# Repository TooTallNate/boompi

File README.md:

# Boompi

Boompi turns a Raspberry Pi into a boombox: a complete, flashable
appliance OS for building your own - Bluetooth/AirPlay/Spotify audio,
a touchscreen now-playing UI, game emulation, battery awareness, and
remote control over Wi-Fi or BLE (web + iOS). It grew out of two
custom builds and is becoming something anyone can put in a box:

- **`boompid`** - Rust backend daemon: Bluetooth (BlueZ), Spotify Connect
  (librespot), AirPlay (shairport-sync), PipeWire volume, INA260 battery
  telemetry, FFT visualizer, album art. Serves a WebSocket/HTTP API.
- **`boompi-ui`** - Slint touchscreen UI: renders directly on DRM/KMS on the
  boombox, or as a desktop app on a laptop for development.
- **`web/`** - settings web app served by the box; **`web-remote/`** - the
  hosted Web Bluetooth remote ([boompi.n8.io](https://boompi.n8.io));
  **`ios/`** - the native iOS app.
- **`buildroot/`** - flashable, pre-configured SD card images (silent boot,
  A/B self-updates, first-boot setup). Box-specific hardware (display
  panel, DAC, battery sensor, wiring) is described by an on-device
  profile, not baked into the image - one image boots every build.

The v1 stack (Node.js + Next.js + Chromium kiosk) lives on the `v1` branch.
The (shipped) design and phased plan is in [`docs/PLAN.md`](docs/PLAN.md),
the A/B update system in [`docs/UPDATES.md`](docs/UPDATES.md), and
future work in [`docs/ROADMAP.md`](docs/ROADMAP.md).

Releases are cut with [changesets](.changeset/README.md): merging the
"Version Packages" PR publishes a GitHub Release with flashable images
and OTA assets; every green build of `main` also refreshes the rolling
`edge` prerelease. The boxes update themselves from either channel
(Settings → Software).

## Development

No hardware needed for UI work:

```sh
make sim   # terminal 1: backend with simulated sources/battery/visualizer
make ui    # terminal 2: the UI, connected to the local sim
```

Against a real boombox:

```sh
make ui BACKEND=ws://boombox.local:3001/ws
```

Other targets: `make check`, `make test`, `make fmt`, `make clippy`.

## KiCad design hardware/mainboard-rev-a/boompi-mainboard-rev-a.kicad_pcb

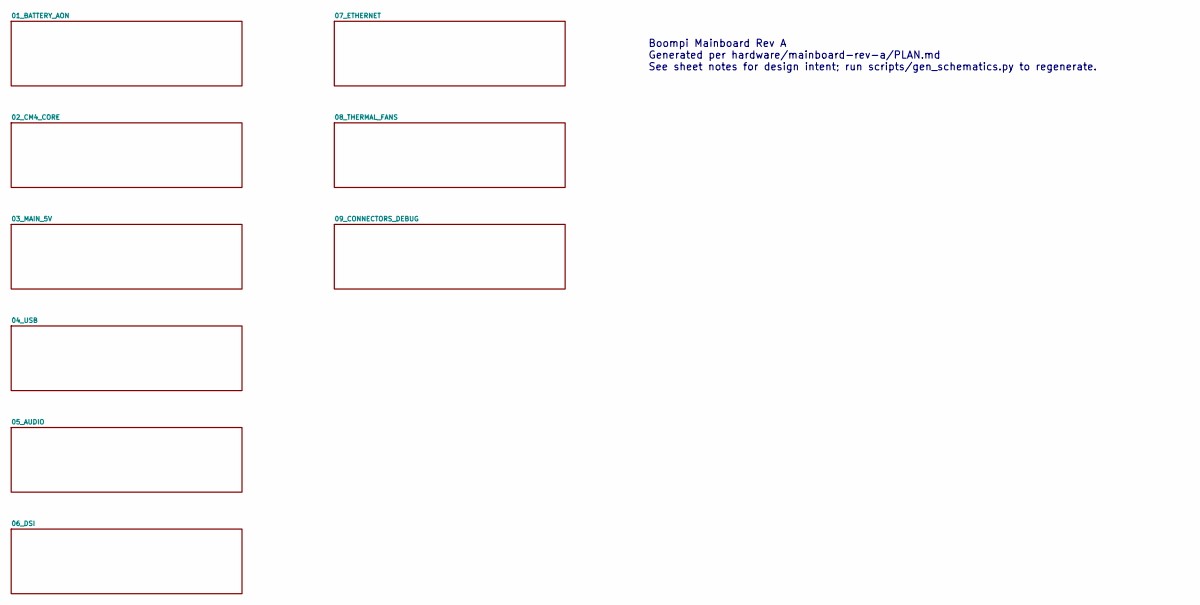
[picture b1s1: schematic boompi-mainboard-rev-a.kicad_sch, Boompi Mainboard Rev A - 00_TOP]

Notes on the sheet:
Boompi Mainboard Rev A Generated per hardware/mainboard-rev-a/PLAN.md See sheet notes for design intent; run scripts/gen_schematics.py to regenerate.

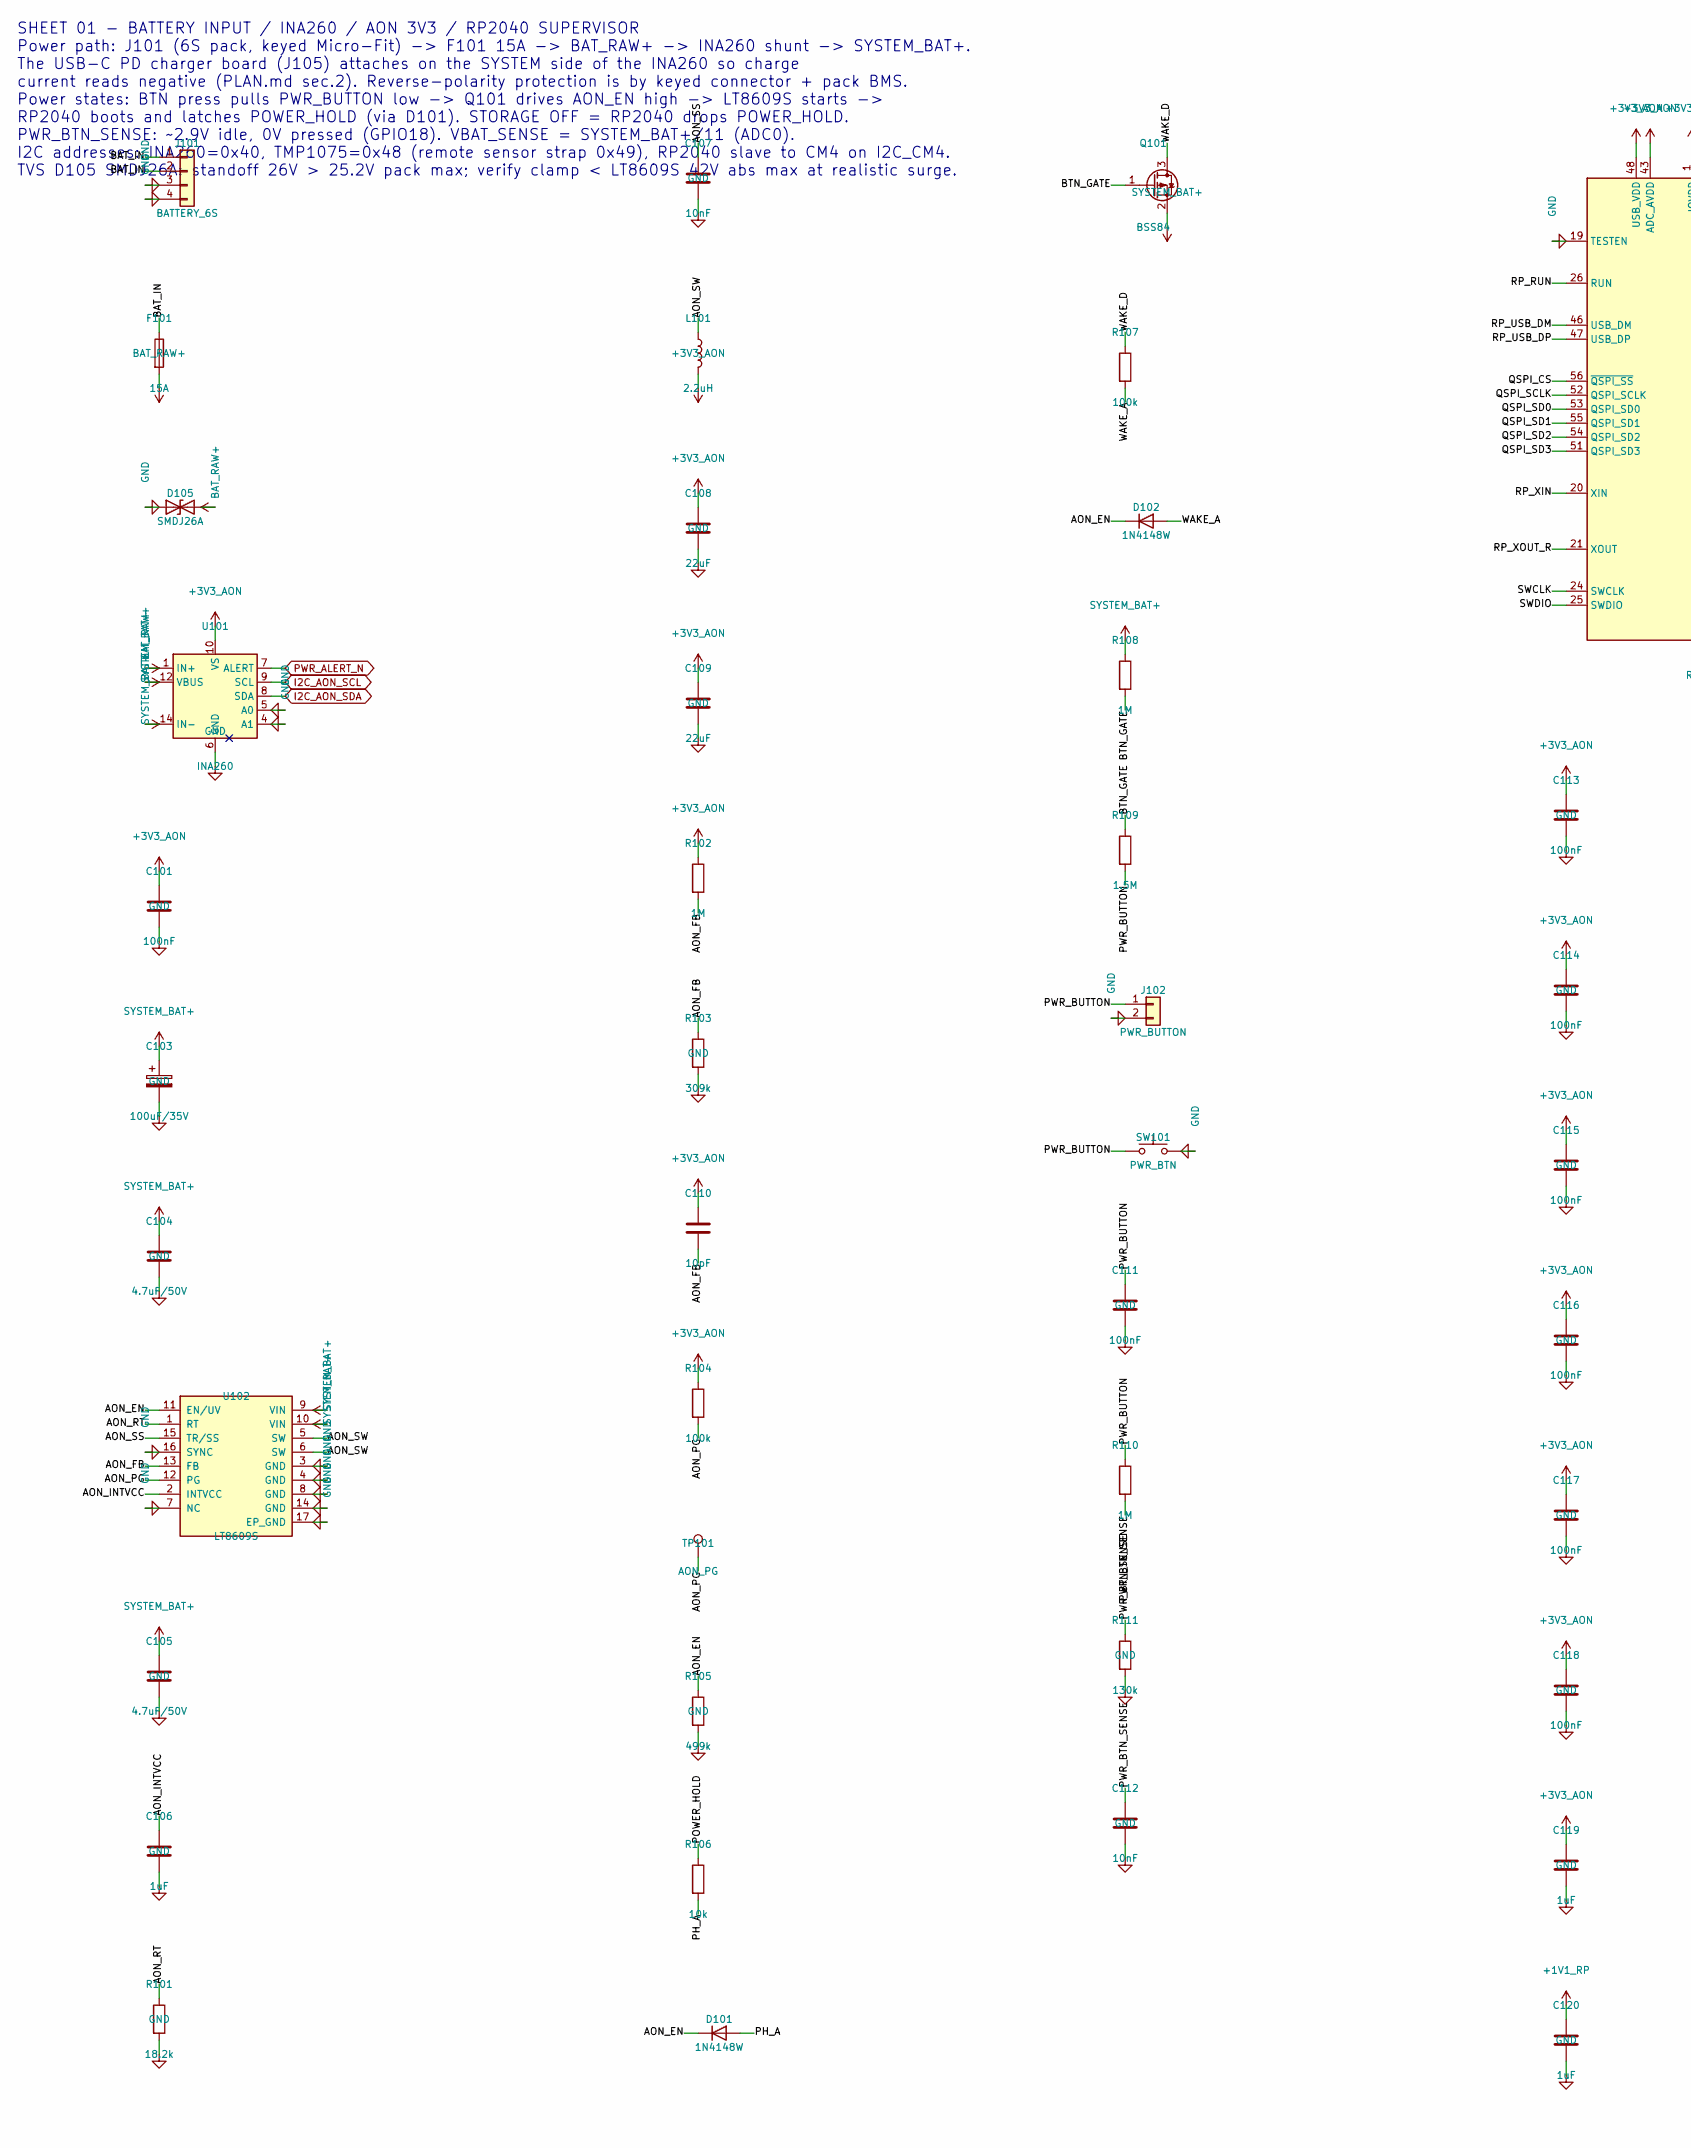
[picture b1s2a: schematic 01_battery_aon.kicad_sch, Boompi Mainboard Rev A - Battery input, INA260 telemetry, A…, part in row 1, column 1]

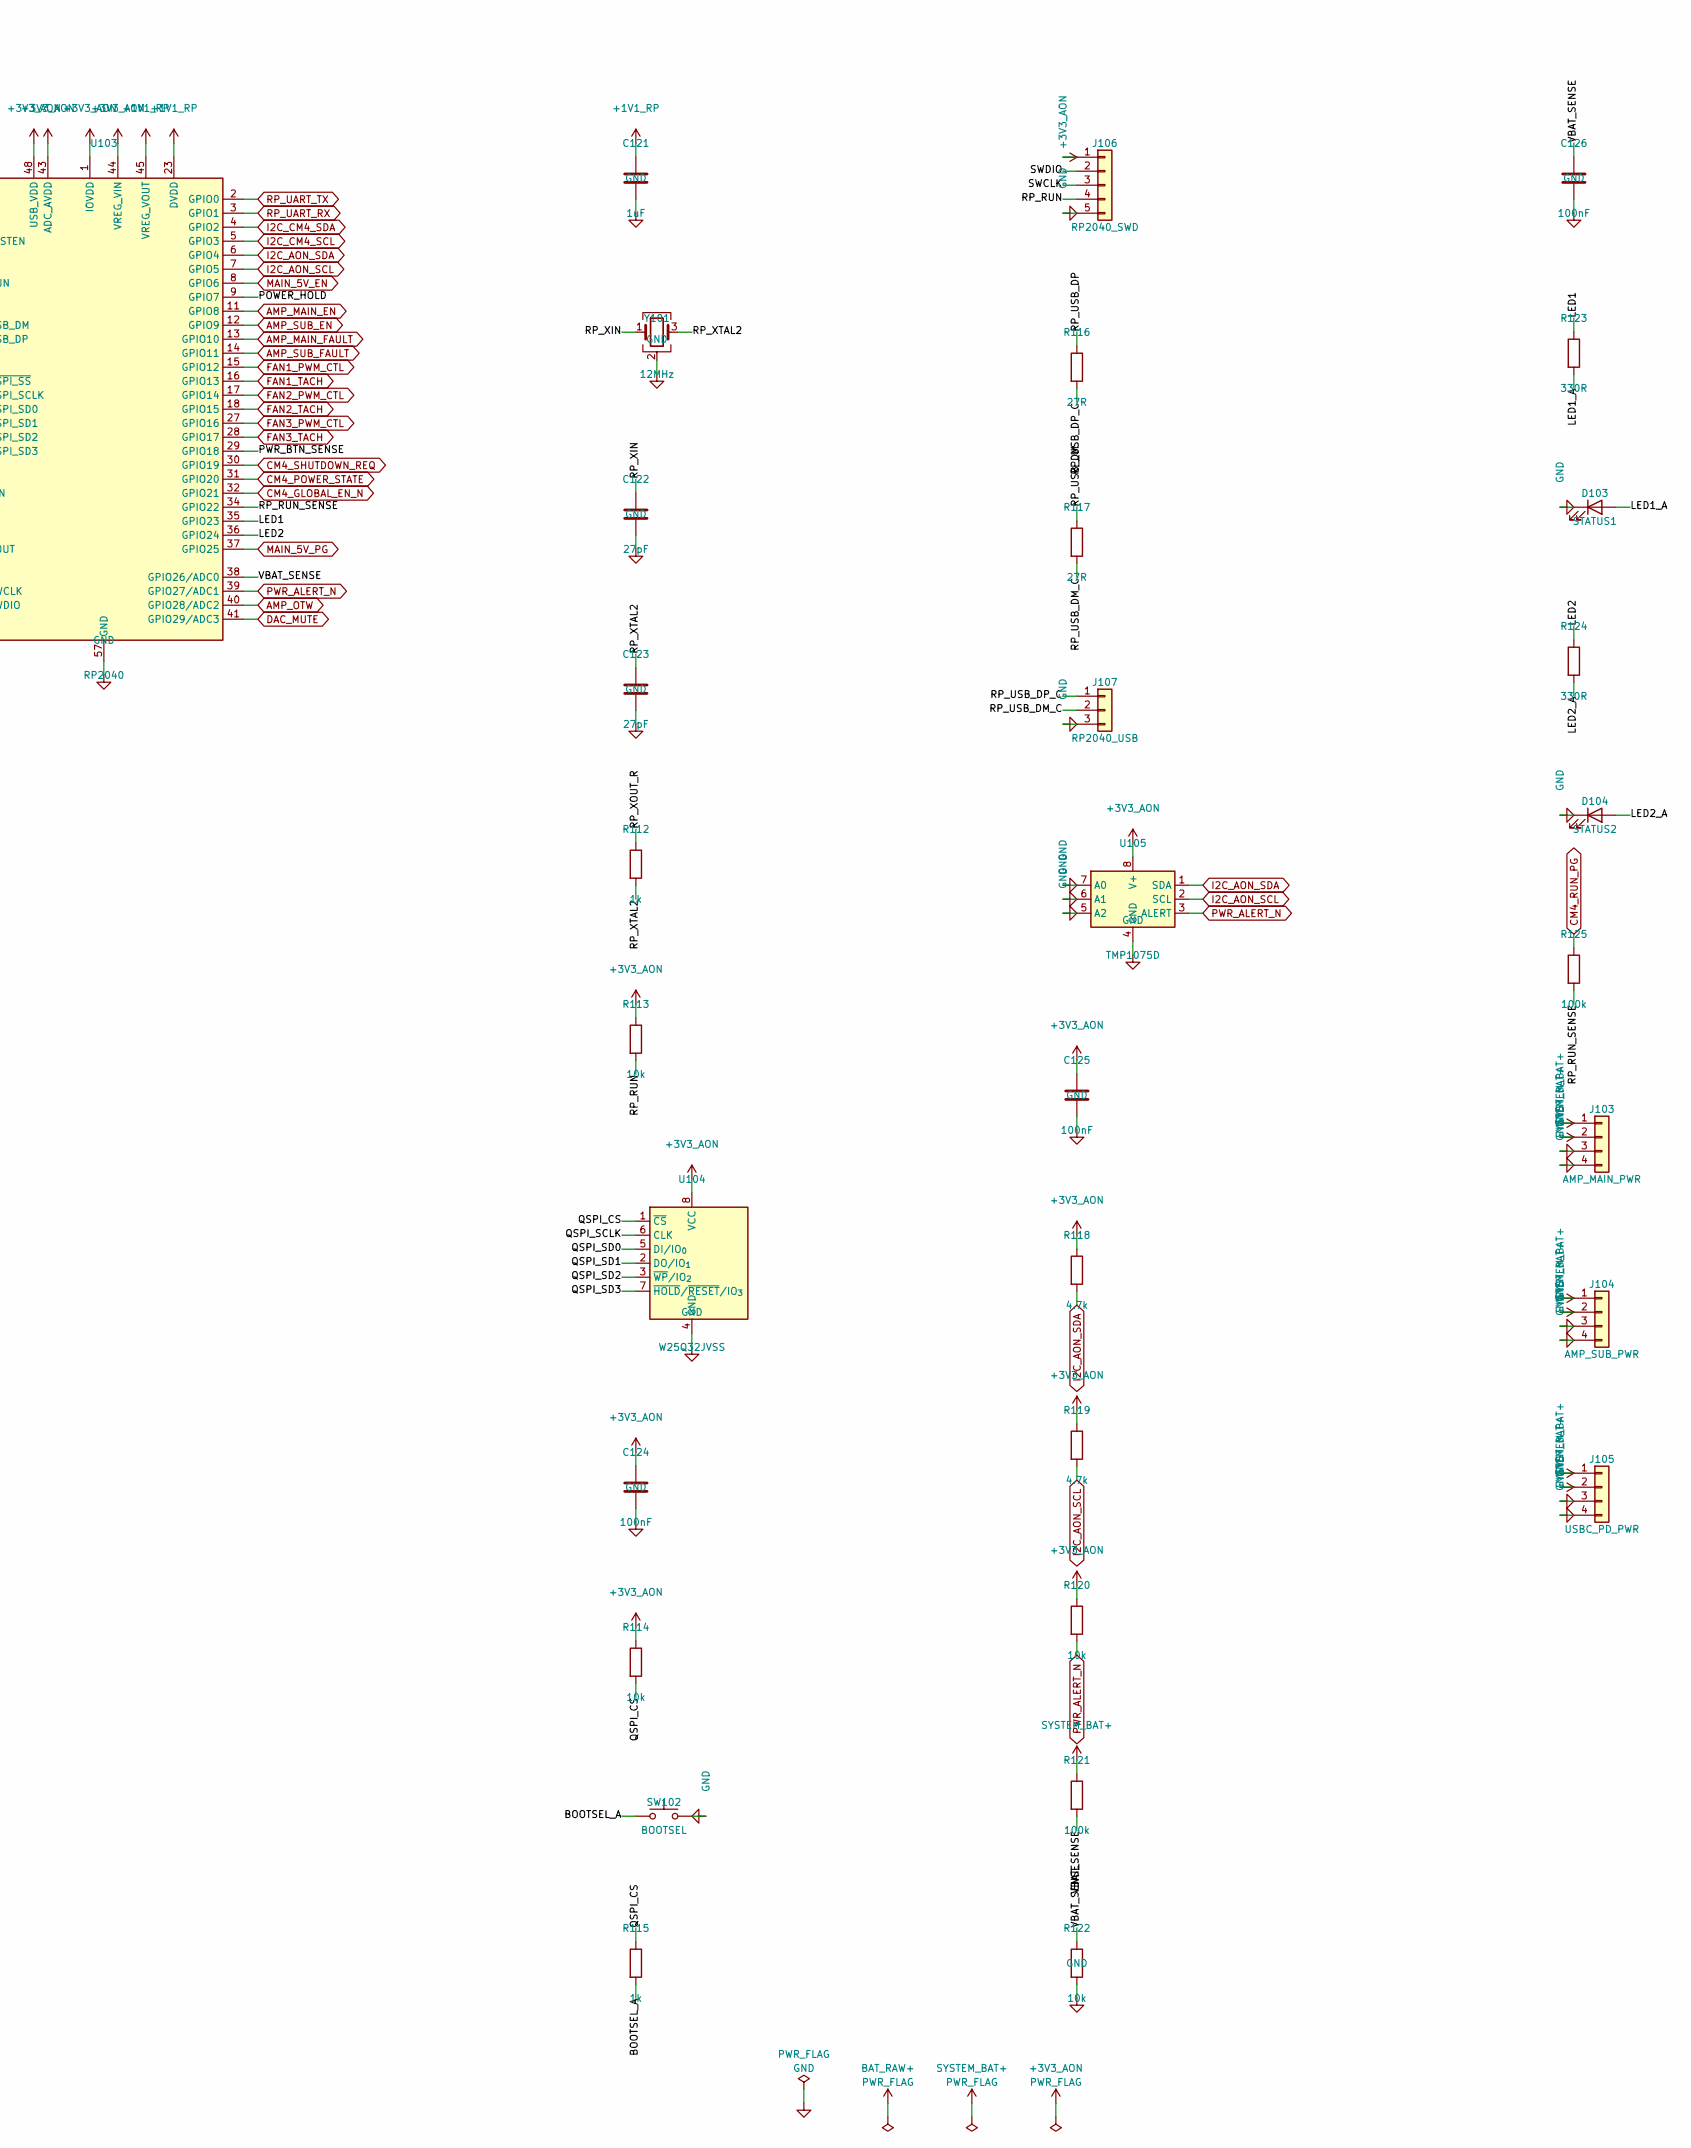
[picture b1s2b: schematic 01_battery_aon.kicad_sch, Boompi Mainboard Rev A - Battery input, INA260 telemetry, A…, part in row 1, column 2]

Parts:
C101, C111, C113, C114, C115, C116, C117, C118, C124, C125, C126: 100nF; C_0603_1608Metric
C103: 100uF/35V; CP_Elec_8x10.5; MPN Panasonic EEE-FK1V101P
C104, C105: 4.7uF/50V; C_1210_3225Metric
C106, C119, C120, C121: 1uF; C_0603_1608Metric
C107, C112: 10nF; C_0603_1608Metric
C108, C109: 22uF; C_1210_3225Metric
C110: 10pF; C_0603_1608Metric
C122, C123: 27pF; C_0603_1608Metric
D101, D102: 1N4148W; D_SOD-123; MPN 1N4148W-7-F
D103: STATUS1; LED_0603_1608Metric
D104: STATUS2; LED_0603_1608Metric
D105: SMDJ26A; D_SMC; MPN Littelfuse SMDJ26A
F101: 15A; Fuse_Littelfuse-NANO2-451_453; MPN Littelfuse 0451015.MRL
J101: BATTERY_6S; Molex_Micro-Fit_3.0_43650-0415_1x04_P3.00mm_Vertical; MPN Molex 43650-0415
J102: PWR_BUTTON; JST_PH_B2B-PH-K_1x02_P2.00mm_Vertical; MPN JST B2B-PH-K-S
J103: AMP_MAIN_PWR; Molex_Micro-Fit_3.0_43650-0415_1x04_P3.00mm_Vertical; MPN Molex 43650-0415
J104: AMP_SUB_PWR; Molex_Micro-Fit_3.0_43650-0415_1x04_P3.00mm_Vertical; MPN Molex 43650-0415
J105: USBC_PD_PWR; Molex_Micro-Fit_3.0_43650-0415_1x04_P3.00mm_Vertical; MPN Molex 43650-0415
J106: RP2040_SWD; PinHeader_1x05_P2.54mm_Vertical
J107: RP2040_USB; PinHeader_1x03_P2.54mm_Vertical
L101: 2.2uH; L_Coilcraft_XxL4020; MPN Coilcraft XFL4020-222ME
Q101: BSS84; SOT-23; MPN onsemi BSS84LT1G
R101: 18.2k; R_0603_1608Metric
R102, R108, R110: 1M; R_0603_1608Metric
R103: 309k; R_0603_1608Metric
R104, R107, R121, R125: 100k; R_0603_1608Metric
R105: 499k; R_0603_1608Metric
R106, R113, R114, R120, R122: 10k; R_0603_1608Metric
R109: 1.5M; R_0603_1608Metric
R111: 130k; R_0603_1608Metric
R112, R115: 1k; R_0603_1608Metric
R116, R117: 27R; R_0603_1608Metric
R118, R119: 4.7k; R_0603_1608Metric
R123, R124: 330R; R_0603_1608Metric
SW101: PWR_BTN; SW_SPST_TL3342; MPN E-Switch TL3342F160QG
SW102: BOOTSEL; SW_SPST_TL3342
TP101: AON_PG; TestPoint_Pad_D1.5mm
U101: INA260; TSSOP-16_4.4x5mm_P0.65mm; MPN TI INA260AIPW
U102: LT8609S; LT8609S_LQFN16_3x3mm; MPN ADI LT8609SEV#PBF
U103: RP2040; QFN-56-1EP_7x7mm_P0.4mm_EP3.2x3.2mm; MPN Raspberry Pi RP2040
U104: W25Q32JVSS; SOIC-8_5.3x5.3mm_P1.27mm; MPN Winbond W25Q32JVSSIQ
U105: TMP1075D; SOIC-8_3.9x4.9mm_P1.27mm; MPN TI TMP1075DR
Y101: 12MHz; Crystal_SMD_3225-4Pin_3.2x2.5mm; MPN Abracon ABM8-12.000MHZ-B2-T

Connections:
+1V1_RP: C120.1, C121.1, U103.23 (DVDD), U103.45 (VREG_VOUT), U103.50 (DVDD)
+3V3_AON: C101.1, C108.1, C109.1, C110.1, C113.1, C114.1, C115.1, C116.1, C117.1, C118.1, C119.1, C124.1, C125.1, J106.1, L101.2, R102.1, R104.1, R113.1, R114.1, R118.1, R119.1, R120.1, U101.10 (VS), U103.1 (IOVDD), U103.10 (IOVDD), U103.22 (IOVDD), U103.33 (IOVDD), U103.42 (IOVDD), U103.43 (ADC_AVDD), U103.44 (VREG_VIN), U103.48 (USB_VDD), U103.49 (IOVDD), U104.8 (VCC), U105.8 (V+); also elsewhere on the board
/01_BATTERY_AON/AON_EN: D101.1 (K), D102.1 (K), R105.1, U102.11 (EN/UV)
/01_BATTERY_AON/AON_FB: C110.2, R102.2, R103.1, U102.13 (FB)
/01_BATTERY_AON/AON_INTVCC: C106.1, U102.2 (INTVCC)
/01_BATTERY_AON/AON_PG: R104.2, TP101.1, U102.12 (PG)
/01_BATTERY_AON/AON_RT: R101.1, U102.1 (RT)
/01_BATTERY_AON/AON_SS: C107.1, U102.15 (TR/SS)
/01_BATTERY_AON/AON_SW: L101.1, U102.5 (SW), U102.6 (SW)
/01_BATTERY_AON/BAT_IN: F101.1, J101.1, J101.2
/01_BATTERY_AON/BOOTSEL_A: R115.2, SW102.1
/01_BATTERY_AON/BTN_GATE: Q101.1 (G), R108.2, R109.1
/01_BATTERY_AON/LED1: R123.1, U103.35 (GPIO23)
/01_BATTERY_AON/LED1_A: D103.2 (A), R123.2
/01_BATTERY_AON/LED2: R124.1, U103.36 (GPIO24)
/01_BATTERY_AON/LED2_A: D104.2 (A), R124.2
/01_BATTERY_AON/PH_A: D101.2 (A), R106.2
/01_BATTERY_AON/POWER_HOLD: R106.1, U103.9 (GPIO7)
/01_BATTERY_AON/PWR_BTN_SENSE: C112.1, R110.2, R111.1, U103.29 (GPIO18)
/01_BATTERY_AON/PWR_BUTTON: C111.1, J102.1, R109.2, R110.1, SW101.1
/01_BATTERY_AON/QSPI_CS: R114.2, R115.1, U103.56 (~QSPI_SS), U104.1 (~CS)
/01_BATTERY_AON/QSPI_SCLK: U103.52 (QSPI_SCLK), U104.6 (CLK)
/01_BATTERY_AON/QSPI_SD0: U103.53 (QSPI_SD0), U104.5 (DI/IO_{0})
/01_BATTERY_AON/QSPI_SD1: U103.55 (QSPI_SD1), U104.2 (DO/IO_{1})
/01_BATTERY_AON/QSPI_SD2: U103.54 (QSPI_SD2), U104.3 (~WP/IO_{2})
/01_BATTERY_AON/QSPI_SD3: U103.51 (QSPI_SD3), U104.7 (~HOLD/~RESET/IO_{3})
/01_BATTERY_AON/RP_RUN: J106.4, R113.2, U103.26 (RUN)
/01_BATTERY_AON/RP_RUN_SENSE: R125.2, U103.34 (GPIO22)
/01_BATTERY_AON/RP_USB_DM: R117.1, U103.46 (USB_DM)
/01_BATTERY_AON/RP_USB_DM_C: J107.2, R117.2
/01_BATTERY_AON/RP_USB_DP: R116.1, U103.47 (USB_DP)
/01_BATTERY_AON/RP_USB_DP_C: J107.1, R116.2
/01_BATTERY_AON/RP_XIN: C122.1, U103.20 (XIN), Y101.1
/01_BATTERY_AON/RP_XOUT_R: R112.1, U103.21 (XOUT)
/01_BATTERY_AON/RP_XTAL2: C123.1, R112.2, Y101.3
/01_BATTERY_AON/SWCLK: J106.3, U103.24 (SWCLK)
/01_BATTERY_AON/SWDIO: J106.2, U103.25 (SWDIO)
/01_BATTERY_AON/VBAT_SENSE: C126.1, R121.2, R122.1, U103.38 (GPIO26/ADC0)
/01_BATTERY_AON/WAKE_A: D102.2 (A), R107.2
/01_BATTERY_AON/WAKE_D: Q101.3 (D), R107.1
AMP_MAIN_EN: U103.11 (GPIO8); also elsewhere on the board
AMP_MAIN_FAULT: U103.13 (GPIO10); also elsewhere on the board
AMP_OTW: U103.40 (GPIO28/ADC2); also elsewhere on the board
AMP_SUB_EN: U103.12 (GPIO9); also elsewhere on the board
AMP_SUB_FAULT: U103.14 (GPIO11); also elsewhere on the board
BAT_RAW+: D105.2 (A2), F101.2, U101.1 (IN+), U101.2 (IN+), U101.3 (IN+)
CM4_GLOBAL_EN_N: U103.32 (GPIO21); also elsewhere on the board
CM4_POWER_STATE: U103.31 (GPIO20); also elsewhere on the board
CM4_RUN_PG: R125.1; also elsewhere on the board
CM4_SHUTDOWN_REQ: U103.30 (GPIO19); also elsewhere on the board
DAC_MUTE: U103.41 (GPIO29/ADC3); also elsewhere on the board
FAN1_PWM_CTL: U103.15 (GPIO12); also elsewhere on the board
FAN1_TACH: U103.16 (GPIO13); also elsewhere on the board
FAN2_PWM_CTL: U103.17 (GPIO14); also elsewhere on the board
FAN2_TACH: U103.18 (GPIO15); also elsewhere on the board
FAN3_PWM_CTL: U103.27 (GPIO16); also elsewhere on the board
FAN3_TACH: U103.28 (GPIO17); also elsewhere on the board
GND: C101.2, C103.2, C104.2, C105.2, C106.2, C107.2, C108.2, C109.2, C111.2, C112.2, C113.2, C114.2, C115.2, C116.2, C117.2, C118.2, C119.2, C120.2, C121.2, C122.2, C123.2, C124.2, C125.2, C126.2, D103.1 (K), D104.1 (K), D105.1 (A1), J101.3, J101.4, J102.2, J103.3, J103.4, J104.3, J104.4, J105.3, J105.4, J106.5, J107.3, R101.2, R103.2, R105.2, R111.2, R122.2, SW101.2, SW102.2, U101.4 (A1), U101.5 (A0), U101.6 (GND), U101.11 (GND), U102.3 (GND), U102.4 (GND), U102.7 (NC), U102.8 (GND), U102.14 (GND), U102.16 (SYNC), U102.17 (EP_GND), U103.19 (TESTEN), U103.57 (GND), U104.4 (GND), U105.4 (GND), U105.5 (A2), U105.6 (A1), U105.7 (A0), Y101.2 (G), Y101.4 (G); also elsewhere on the board
I2C_AON_SCL: R119.2, U101.9 (SCL), U103.7 (GPIO5), U105.2 (SCL); also elsewhere on the board
I2C_AON_SDA: R118.2, U101.8 (SDA), U103.6 (GPIO4), U105.1 (SDA); also elsewhere on the board
I2C_CM4_SCL: U103.5 (GPIO3); also elsewhere on the board
I2C_CM4_SDA: U103.4 (GPIO2); also elsewhere on the board
MAIN_5V_EN: U103.8 (GPIO6); also elsewhere on the board
MAIN_5V_PG: U103.37 (GPIO25); also elsewhere on the board
PWR_ALERT_N: R120.2, U101.7 (ALERT), U103.39 (GPIO27/ADC1), U105.3 (ALERT)
RP_UART_RX: U103.3 (GPIO1); also elsewhere on the board
RP_UART_TX: U103.2 (GPIO0); also elsewhere on the board
SYSTEM_BAT+: C103.1, C104.1, C105.1, J103.1, J103.2, J104.1, J104.2, J105.1, J105.2, Q101.2 (S), R108.1, R121.1, U101.12 (VBUS), U101.14 (IN-), U101.15 (IN-), U101.16 (IN-), U102.9 (VIN), U102.10 (VIN); also elsewhere on the board

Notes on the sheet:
SHEET 01 - BATTERY INPUT / INA260 / AON 3V3 / RP2040 SUPERVISOR Power path: J101 (6S pack, keyed Micro-Fit) -> F101 15A -> BAT_RAW+ -> INA260 shunt -> SYSTEM_BAT+. The USB-C PD charger board (J105) attaches on the SYSTEM side of the INA260 so charge current reads negative (PLAN.md sec.2). Reverse-p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

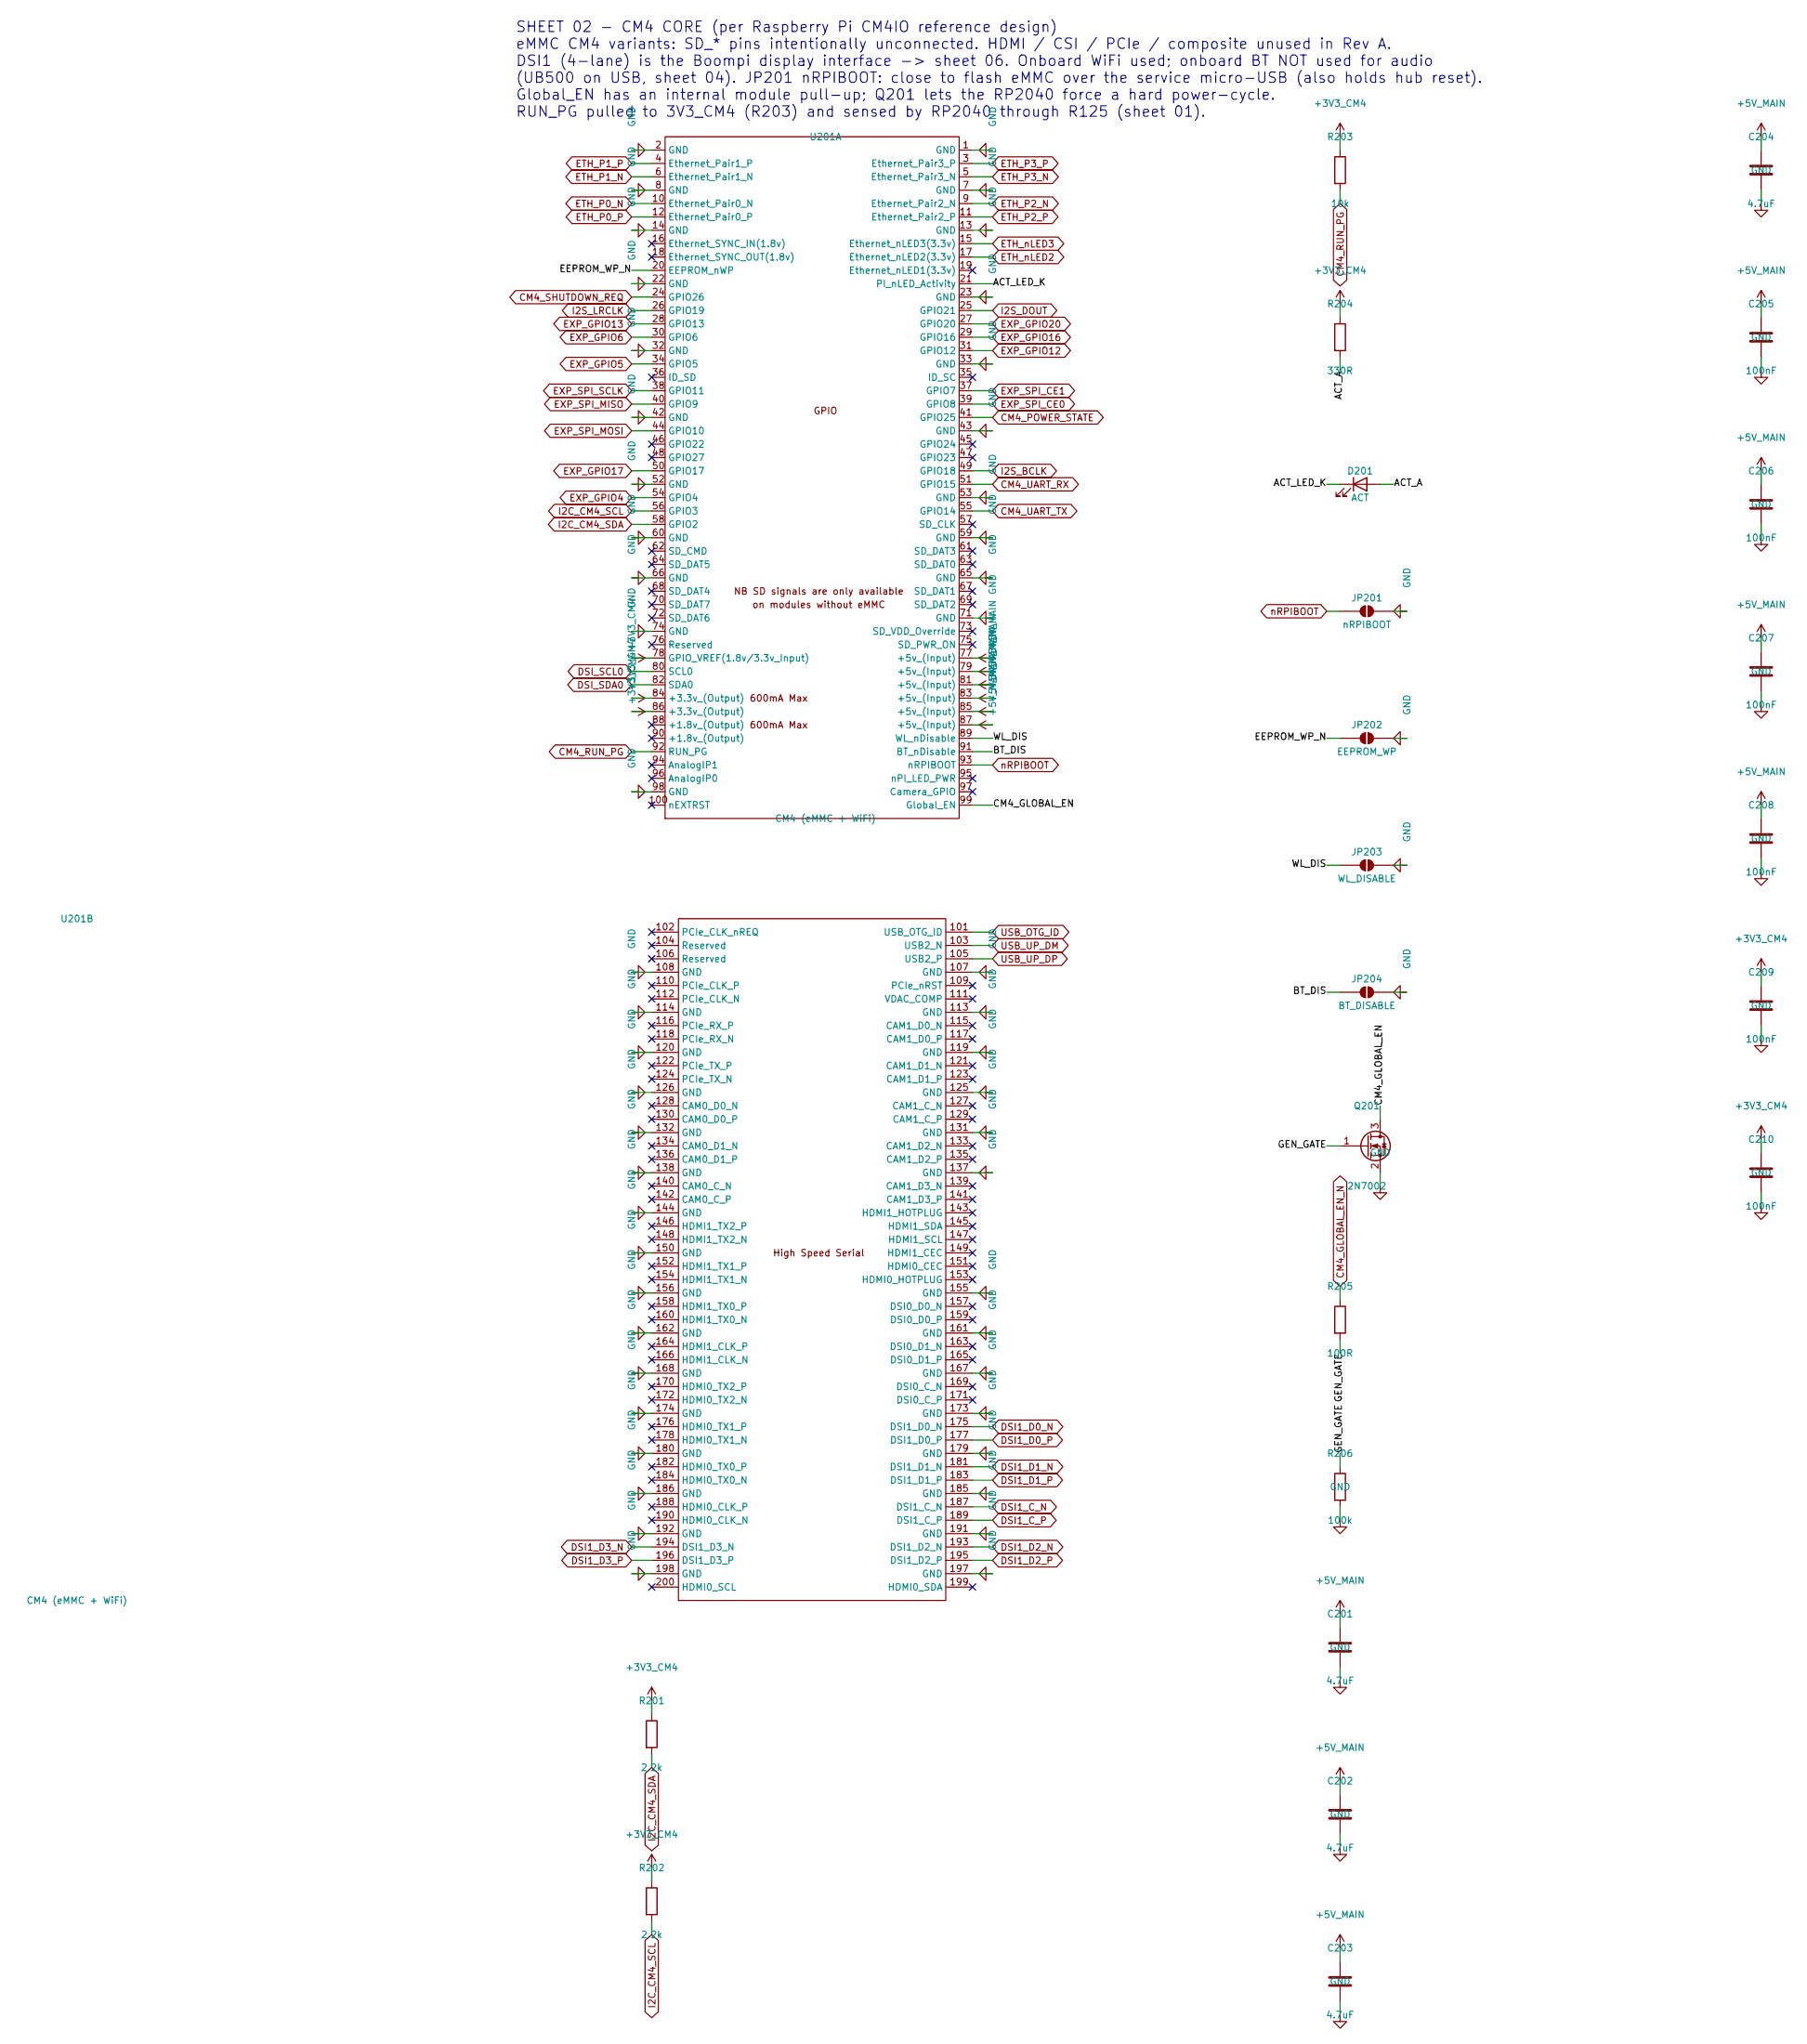
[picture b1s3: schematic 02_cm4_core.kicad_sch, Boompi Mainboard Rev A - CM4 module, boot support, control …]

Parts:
C201, C202, C203, C204: 4.7uF; C_0805_2012Metric
C205, C206, C207, C208, C209, C210: 100nF; C_0603_1608Metric
D201: ACT; LED_0603_1608Metric
JP201: nRPIBOOT; SolderJumper-2_P1.3mm_Open_TrianglePad1.0x1.5mm
JP202: EEPROM_WP; SolderJumper-2_P1.3mm_Open_TrianglePad1.0x1.5mm
JP203: WL_DISABLE; SolderJumper-2_P1.3mm_Open_TrianglePad1.0x1.5mm
JP204: BT_DISABLE; SolderJumper-2_P1.3mm_Open_TrianglePad1.0x1.5mm
Q201: 2N7002; SOT-23
R201, R202: 2.2k; R_0603_1608Metric
R203: 10k; R_0603_1608Metric
R204: 330R; R_0603_1608Metric
R205: 100R; R_0603_1608Metric
R206: 100k; R_0603_1608Metric
U201: CM4 (eMMC + WiFi); Raspberry-Pi-4-Compute-Module; MPN Raspberry Pi CM4104032

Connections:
+3V3_CM4: C209.1, C210.1, R201.1, R202.1, R203.1, R204.1, U201.78 (GPIO_VREF(1.8v/3.3v_Input)), U201.84 (+3.3v_(Output)), U201.86 (+3.3v_(Output)); also elsewhere on the board
+5V_MAIN: C201.1, C202.1, C203.1, C204.1, C205.1, C206.1, C207.1, C208.1, U201.77 (+5v_(Input)), U201.79 (+5v_(Input)), U201.81 (+5v_(Input)), U201.83 (+5v_(Input)), U201.85 (+5v_(Input)), U201.87 (+5v_(Input)); also elsewhere on the board
/02_CM4_CORE/ACT_A: D201.2 (A), R204.2
/02_CM4_CORE/ACT_LED_K: D201.1 (K), U201.21 (PI_nLED_Activity)
/02_CM4_CORE/BT_DIS: JP204.1 (A), U201.91 (BT_nDisable)
/02_CM4_CORE/CM4_GLOBAL_EN: Q201.3 (D), U201.99 (Global_EN)
/02_CM4_CORE/EEPROM_WP_N: JP202.1 (A), U201.20 (EEPROM_nWP)
/02_CM4_CORE/GEN_GATE: Q201.1 (G), R205.2, R206.1
/02_CM4_CORE/WL_DIS: JP203.1 (A), U201.89 (WL_nDisable)
CM4_GLOBAL_EN_N: R205.1; also elsewhere on the board
CM4_POWER_STATE: U201.41 (GPIO25); also elsewhere on the board
CM4_RUN_PG: R203.2, U201.92 (RUN_PG); also elsewhere on the board
CM4_SHUTDOWN_REQ: U201.24 (GPIO26); also elsewhere on the board
CM4_UART_RX: U201.51 (GPIO15); also elsewhere on the board
CM4_UART_TX: U201.55 (GPIO14); also elsewhere on the board
DSI1_C_N: U201.187 (DSI1_C_N); also elsewhere on the board
DSI1_C_P: U201.189 (DSI1_C_P); also elsewhere on the board
DSI1_D0_N: U201.175 (DSI1_D0_N); also elsewhere on the board
DSI1_D0_P: U201.177 (DSI1_D0_P); also elsewhere on the board
DSI1_D1_N: U201.181 (DSI1_D1_N); also elsewhere on the board
DSI1_D1_P: U201.183 (DSI1_D1_P); also elsewhere on the board
DSI1_D2_N: U201.193 (DSI1_D2_N); also elsewhere on the board
DSI1_D2_P: U201.195 (DSI1_D2_P); also elsewhere on the board
DSI1_D3_N: U201.194 (DSI1_D3_N); also elsewhere on the board
DSI1_D3_P: U201.196 (DSI1_D3_P); also elsewhere on the board
DSI_SCL0: U201.80 (SCL0); also elsewhere on the board
DSI_SDA0: U201.82 (SDA0); also elsewhere on the board
ETH_P0_N: U201.10 (Ethernet_Pair0_N); also elsewhere on the board
ETH_P0_P: U201.12 (Ethernet_Pair0_P); also elsewhere on the board
ETH_P1_N: U201.6 (Ethernet_Pair1_N); also elsewhere on the board
ETH_P1_P: U201.4 (Ethernet_Pair1_P); also elsewhere on the board
ETH_P2_N: U201.9 (Ethernet_Pair2_N); also elsewhere on the board
ETH_P2_P: U201.11 (Ethernet_Pair2_P); also elsewhere on the board
ETH_P3_N: U201.5 (Ethernet_Pair3_N); also elsewhere on the board
ETH_P3_P: U201.3 (Ethernet_Pair3_P); also elsewhere on the board
ETH_nLED2: U201.17 (Ethernet_nLED2(3.3v)); also elsewhere on the board
ETH_nLED3: U201.15 (Ethernet_nLED3(3.3v)); also elsewhere on the board
EXP_GPIO4: U201.54 (GPIO4); also elsewhere on the board
EXP_GPIO5: U201.34 (GPIO5); also elsewhere on the board
EXP_GPIO6: U201.30 (GPIO6); also elsewhere on the board
EXP_GPIO12: U201.31 (GPIO12); also elsewhere on the board
EXP_GPIO13: U201.28 (GPIO13); also elsewhere on the board
EXP_GPIO16: U201.29 (GPIO16); also elsewhere on the board
EXP_GPIO17: U201.50 (GPIO17); also elsewhere on the board
EXP_GPIO20: U201.27 (GPIO20); also elsewhere on the board
EXP_SPI_CE0: U201.39 (GPIO8); also elsewhere on the board
EXP_SPI_CE1: U201.37 (GPIO7); also elsewhere on the board
EXP_SPI_MISO: U201.40 (GPIO9); also elsewhere on the board
EXP_SPI_MOSI: U201.44 (GPIO10); also elsewhere on the board
EXP_SPI_SCLK: U201.38 (GPIO11); also elsewhere on the board
GND: C201.2, C202.2, C203.2, C204.2, C205.2, C206.2, C207.2, C208.2, C209.2, C210.2, JP201.2 (B), JP202.2 (B), JP203.2 (B), JP204.2 (B), Q201.2 (S), R206.2, U201.1 (GND), U201.2 (GND), U201.7 (GND), U201.8 (GND), U201.13 (GND), U201.14 (GND), U201.22 (GND), U201.23 (GND), U201.32 (GND), U201.33 (GND), U201.42 (GND), U201.43 (GND), U201.52 (GND), U201.53 (GND), U201.59 (GND), U201.60 (GND), U201.65 (GND), U201.66 (GND), U201.71 (GND), U201.74 (GND), U201.98 (GND), U201.107 (GND), U201.108 (GND), U201.113 (GND), U201.114 (GND), U201.119 (GND), U201.120 (GND), U201.125 (GND), U201.126 (GND), U201.131 (GND), U201.132 (GND), U201.137 (GND), U201.138 (GND), U201.144 (GND), U201.150 (GND), U201.155 (GND), U201.156 (GND), U201.161 (GND), U201.162 (GND), U201.167 (GND), U201.168 (GND), U201.173 (GND), U201.174 (GND), U201.179 (GND), U201.180 (GND), U201.185 (GND), U201.186 (GND), U201.191 (GND), U201.192 (GND), U201.197 (GND), U201.198 (GND); also elsewhere on the board
I2C_CM4_SCL: R202.2, U201.56 (GPIO3); also elsewhere on the board
I2C_CM4_SDA: R201.2, U201.58 (GPIO2); also elsewhere on the board
I2S_BCLK: U201.49 (GPIO18); also elsewhere on the board
I2S_DOUT: U201.25 (GPIO21); also elsewhere on the board
I2S_LRCLK: U201.26 (GPIO19); also elsewhere on the board
USB_OTG_ID: U201.101 (USB_OTG_ID); also elsewhere on the board
USB_UP_DM: U201.103 (USB2_N); also elsewhere on the board
USB_UP_DP: U201.105 (USB2_P); also elsewhere on the board
nRPIBOOT: JP201.1 (A), U201.93 (nRPIBOOT); also elsewhere on the board

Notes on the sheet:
SHEET 02 - CM4 CORE (per Raspberry Pi CM4IO reference design) eMMC CM4 variants: SD_* pins intentionally unconnected. HDMI / CSI / PCIe / composite unused in Rev A. DSI1 (4-lane) is the Boompi display interface -> sheet 06. Onboard WiFi used; onboard BT NOT used for audio (UB500 on USB, sheet 04). 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
